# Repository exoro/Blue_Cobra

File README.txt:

Repository contains project files for Blue Cobra

IAR Embedded workbench for STM32F103

Eagle folder contains board and schematics 

ph.alexandersson@gmail.com

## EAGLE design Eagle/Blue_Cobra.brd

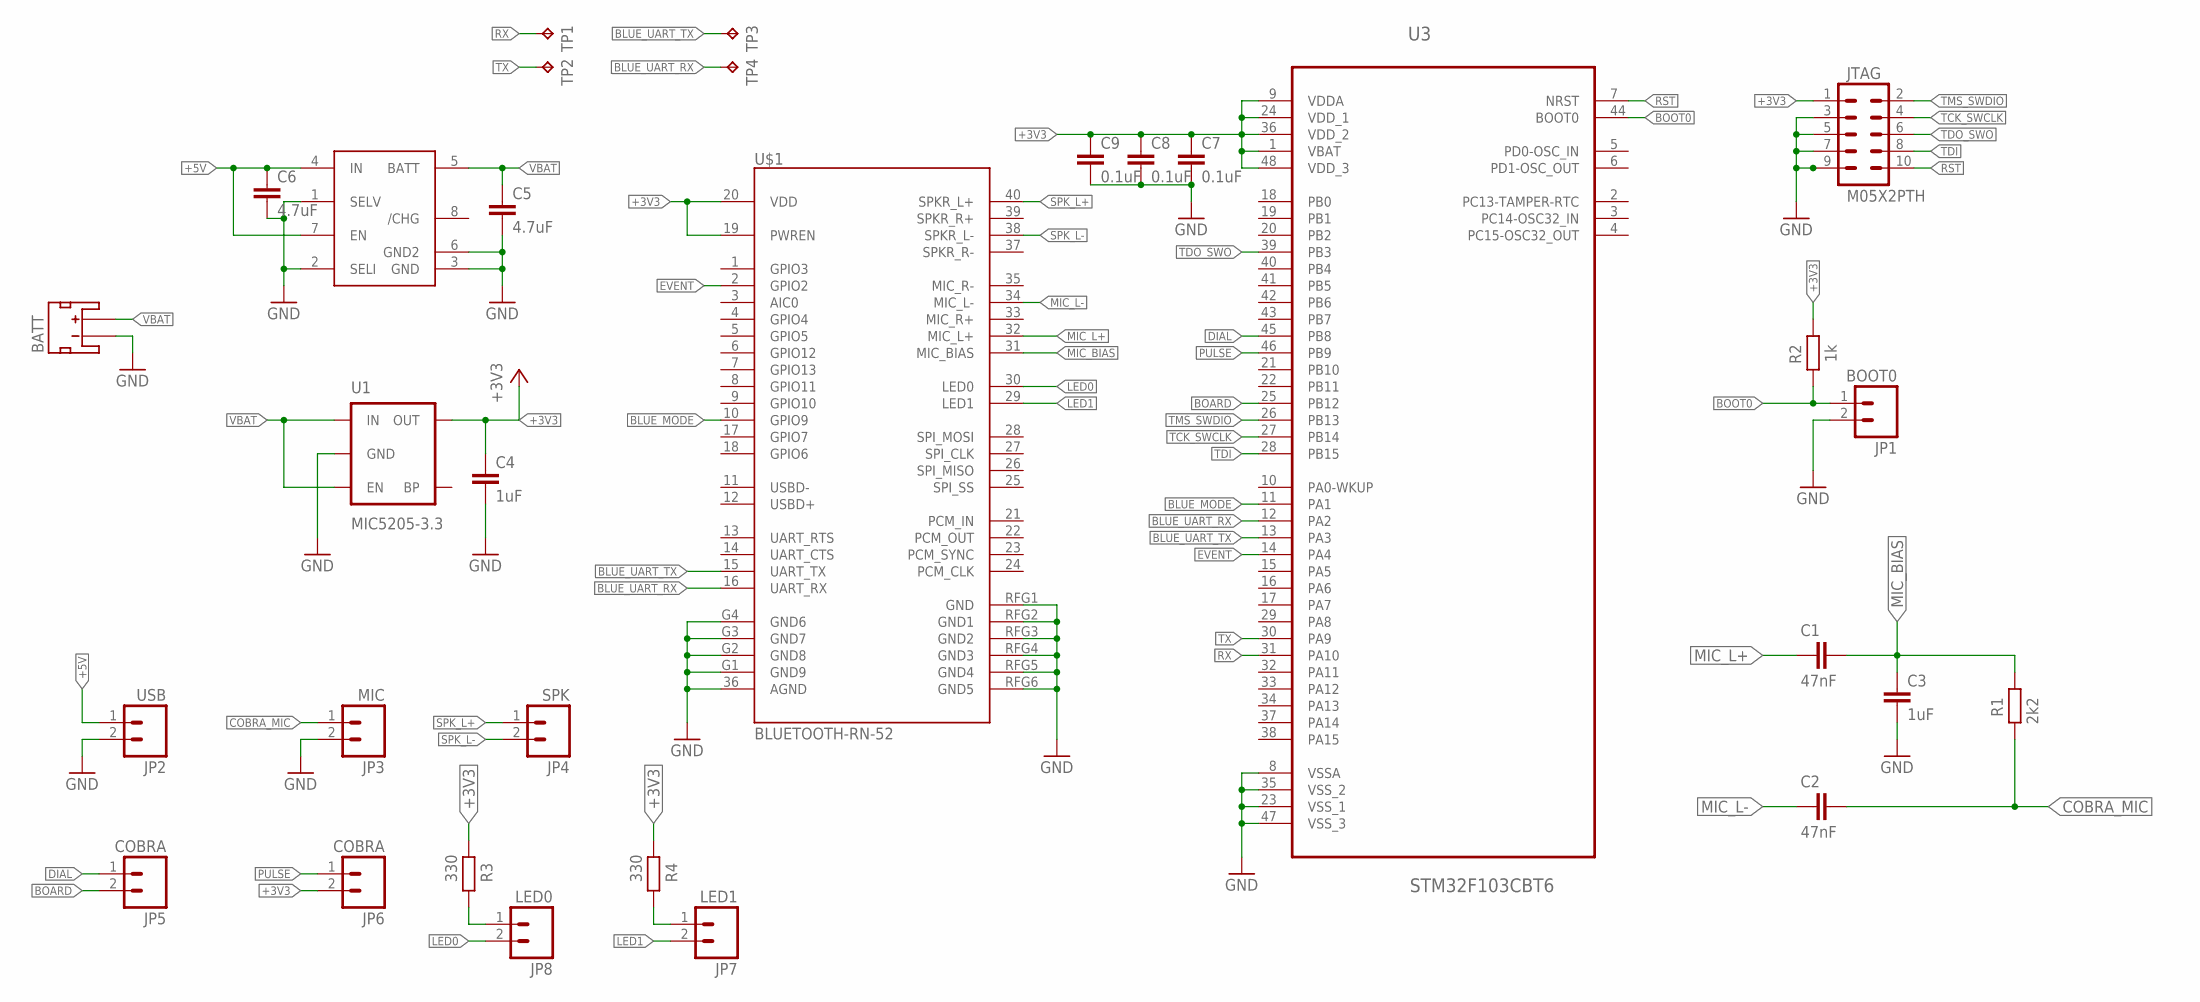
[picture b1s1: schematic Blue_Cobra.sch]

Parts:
BATT: JST_2MM_MALE; JST-2-SMD
C1, C2: 47nF; C0805
C3, C4: 1uF; C0805
C5, C6: 4.7uF; C0805
C7, C8, C9: 0.1uF; C0805
JP1: BOOT0; 1X02_NO_SILK
JP2: USB; 1X02_NO_SILK
JP3: MIC; 1X02_NO_SILK
JP4: SPK; 1X02_NO_SILK
JP5, JP6: COBRA; 1X02_NO_SILK
JP7: LED1; 1X02_NO_SILK
JP8: LED0; 1X02_NO_SILK
JTAG: M05X2PTH; AVR_ICSP
R1: 2k2; R0805
R2: 1k; R0805
R3, R4: 330; R0805
TP1, TP2, TP3, TP4: TPTP10SQ; TP10SQ
U1: MIC5205-3.3; SOT23-5
U2: MAX1811SO8; SO08
U3: STM32F103CBT6; QFP50P900X900X160-48N
U$1: BLUETOOTH-RN-52; RN-52

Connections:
+3V3: C4.1, C7.1, C8.1, C9.1, JP6.2, JTAG.1, R2.2, R3.1, R4.1, U1.5 (OUT), U3.1 (VBAT), U3.9 (VDDA), U3.24 (VDD_1), U3.36 (VDD_2), U3.48 (VDD_3), U$1.19 (PWREN), U$1.20 (VDD)
+5V: C6.1, JP2.1, U2.4 (IN), U2.7 (EN)
BLUE_MODE: U3.11 (PA1), U$1.10 (GPIO9)
BLUE_UART_RX: TP4.TP, U3.12 (PA2), U$1.16 (UART_RX)
BLUE_UART_TX: TP3.TP, U3.13 (PA3), U$1.15 (UART_TX)
BOARD: JP5.2, U3.25 (PB12)
BOOT0: JP1.1, R2.1, U3.44 (BOOT0)
COBRA_MIC: C2.2, JP3.1, R1.1
DIAL: JP5.1, U3.45 (PB8)
EVENT: U3.14 (PA4), U$1.2 (GPIO2)
GND: BATT.1 (-), C3.2, C4.2, C5.2, C6.2, C7.2, C8.2, C9.2, JP1.2, JP2.2, JP3.2, JTAG.3, JTAG.5, JTAG.7, JTAG.9, U1.2 (GND), U2.1 (SELV), U2.2 (SELI), U2.3 (GND), U2.6 (GND2), U3.8 (VSSA), U3.23 (VSS_1), U3.35 (VSS_2), U3.47 (VSS_3), U$1.36 (AGND), U$1.G1 (GND9), U$1.G2 (GND8), U$1.G3 (GND7), U$1.G4 (GND6), U$1.RFG1 (GND), U$1.RFG2 (GND1), U$1.RFG3 (GND2), U$1.RFG4 (GND3), U$1.RFG5 (GND4), U$1.RFG6 (GND5)
LED0: JP8.2, U$1.30 (LED0)
LED1: JP7.2, U$1.29 (LED1)
MIC_BIAS: C1.2, C3.1, R1.2, U$1.31 (MIC_BIAS)
MIC_L+: C1.1, U$1.32 (MIC_L+)
MIC_L-: C2.1, U$1.34 (MIC_L-)
unnamed: JP8.1, R3.2
unnamed: JP7.1, R4.2
PA11: U3.32 (PA11)
PULSE: JP6.1, U3.46 (PB9)
RST: JTAG.10, U3.7 (NRST)
RX: TP1.TP, U3.31 (PA10)
SPK_L+: JP4.1, U$1.40 (SPKR_L+)
SPK_L-: JP4.2, U$1.38 (SPKR_L-)
TCK_SWCLK: JTAG.4, U3.27 (PB14)
TDI: JTAG.8, U3.28 (PB15)
TDO_SWO: JTAG.6, U3.39 (PB3)
TMS_SWDIO: JTAG.2, U3.26 (PB13)
TX: TP2.TP, U3.30 (PA9)
VBAT: BATT.2 (+), C5.1, U1.1 (IN), U1.3 (EN), U2.5 (BATT)

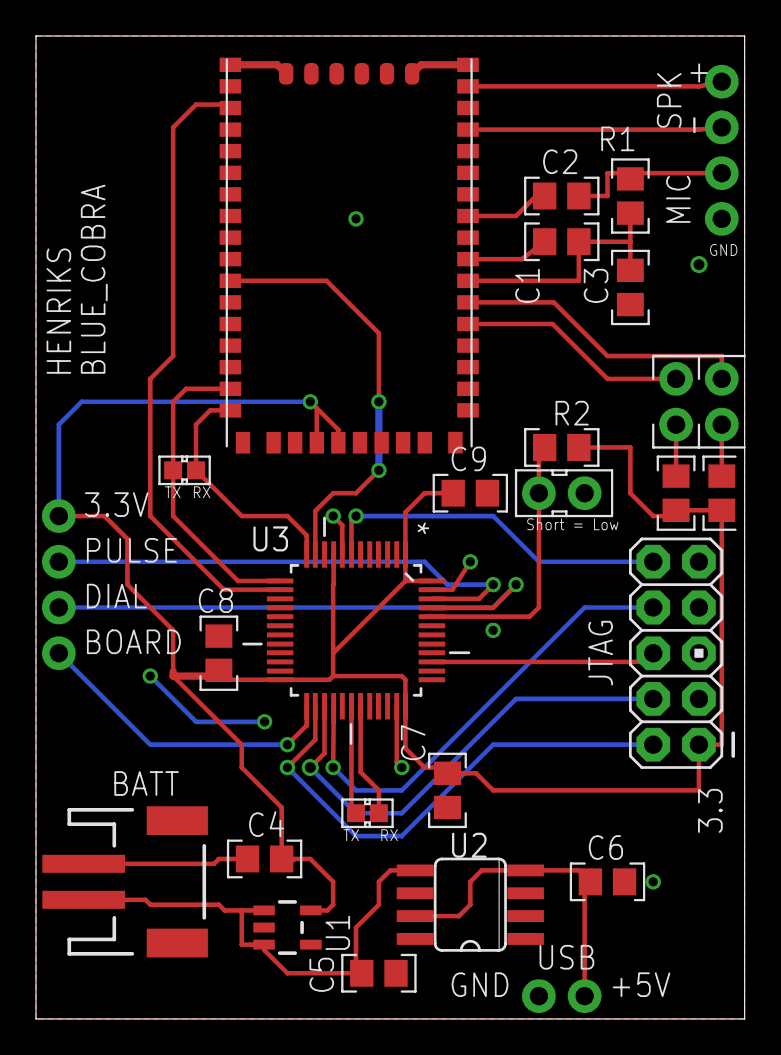
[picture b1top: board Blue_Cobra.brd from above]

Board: 2 copper layers, 39.4 x 54.6 mm, 31 parts (0 on the bottom side), 29 nets.

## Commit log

2014-05-07 Creation of rep
2014-05-07 Added Eagle files
    Board and schematics files for Eagle PCB
2014-05-07 Added Eagle files

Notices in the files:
parts and their libraries:
SparkFun-RF: Licensing: CC v3.0 Share-Alike You are welcome to use this library for commercial purposes.
